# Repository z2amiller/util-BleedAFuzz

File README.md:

# util-BleedAFuzz

A plug-in NPN transistor that biases like a lower-hFE part. In a
single-transistor fuzz with collector-feedback bias (a large resistor from
collector to base), the transistor's hFE mostly decides the DC collector
voltage, not the gain. So when everyone says a circuit "sounds best with a
125 hFE transistor" and all you have is 300s and 600s, what you actually need
is the collector voltage a 125 would give. This board gets you there with a
trimmer.

## How it works

Q1 is wired straight across the header. A fixed 1M plus a 1M trimmer from base
to emitter bleeds a settable share of the base drive, so the feedback resistor
has to supply more current and the collector rises exactly as it would with a
lower-hFE part. The bleed spans 1M to 2M. Effective hFE at a 50 µA stage:

| Bleed | BC847C (~600) | 2SC1815-GR (~300) |
| ----- | ------------- | ----------------- |
| 1M    | ~80           | ~70               |
| 2M    | ~140          | ~110              |

LEAK is an optional 2.2M collector-base resistor that mimics germanium
collector leakage (leave it off unless wanted).

Header order is E, B, C; plug a BC-series (C, B, E) socket in reversed.

## Example: PedalPCB Overcast Fuzz

PedalPCB's [Overcast Fuzz](https://www.pedalpcb.com/product/pcb724/)
([build doc](https://docs.pedalpcb.com/project/OvercastFuzz-PedalPCB.pdf)) is a
Spirit in the Sky style fuzz: one gain transistor with 6M collector-to-base
bias, a 470R emitter resistor and a 100K collector load, and the forum
consensus is that it sounds best around hFE 125. With a 2SC1815-GR (hFE ~300) the
collector sits near 2.0 V; a 125 hFE part would put it near 3.3 V with the
gain control at minimum. Plug this board into the Q1 socket, put a meter on
the collector, and trim until it reads about 3.3 V to nail the 125 hFE sound.

For circuits where the transistor's input impedance matters too (a Fuzz Face
Q1 fed straight from the pickup), the companion
[util-DialAFuzz](https://github.com/z2amiller/util-DialAFuzz) is the better
tool.

## Gerbers

[GERBER-util-BleedAFuzz.zip](GERBER-util-BleedAFuzz.zip) is the JLCPCB-ready
gerber and drill set; no KiCad install needed to order the board. One SOT-23
transistor, two 0805 resistors (one optional), a 3-pin header and a through-hole 1M
trimmer on the back.

## License

Licensed under the **CERN Open Hardware Licence Version 2 – Permissive**
(CERN-OHL-P v2). See [LICENSE](LICENSE) and [NOTICE](NOTICE).

You may make, modify, and sell boards from these files, with no obligation to
publish your changes.

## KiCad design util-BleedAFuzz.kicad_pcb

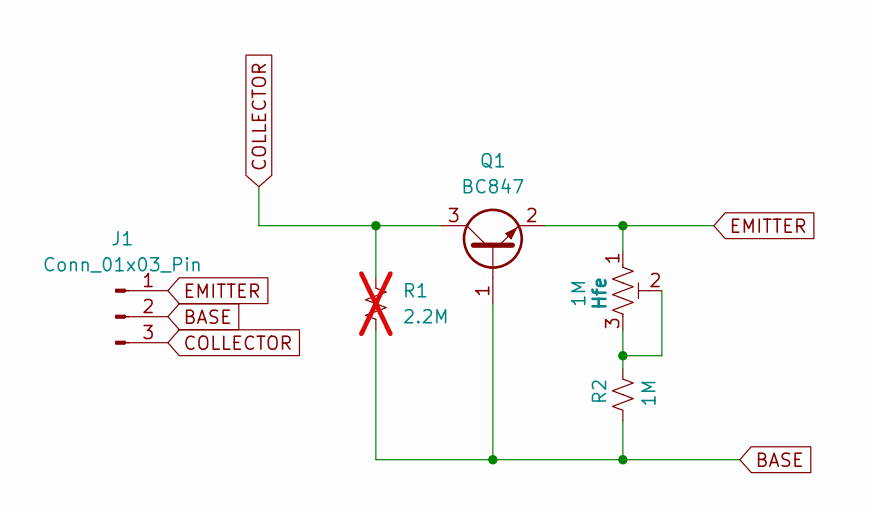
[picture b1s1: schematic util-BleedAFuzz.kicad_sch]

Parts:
J1: Conn_01x03_Pin; PinHeader_1x03_P2.54mm_Vertical
Q1: BC847; SOT-23_Handsoldering
R1: 2.2M; R_0805_2012Metric_Pad1.20x1.40mm_HandSolder; not fitted
R2: 1M; R_0805_2012Metric_Pad1.20x1.40mm_HandSolder
RV1: 1M; Variable Trimmer

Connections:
BASE: J1.2, Q1.1 (B), R1.1, R2.1
COLLECTOR: J1.3, Q1.3 (C), R1.2
EMITTER: J1.1, Q1.2 (E), RV1.1
unnamed: R2.2, RV1.2, RV1.3

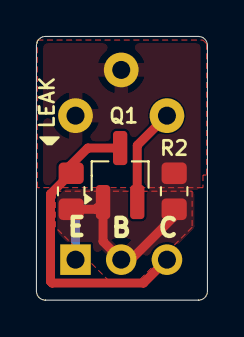
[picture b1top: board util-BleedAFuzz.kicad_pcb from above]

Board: 2 copper layers, 9.5 x 14.7 mm, 5 parts (1 on the bottom side), 4 nets.
